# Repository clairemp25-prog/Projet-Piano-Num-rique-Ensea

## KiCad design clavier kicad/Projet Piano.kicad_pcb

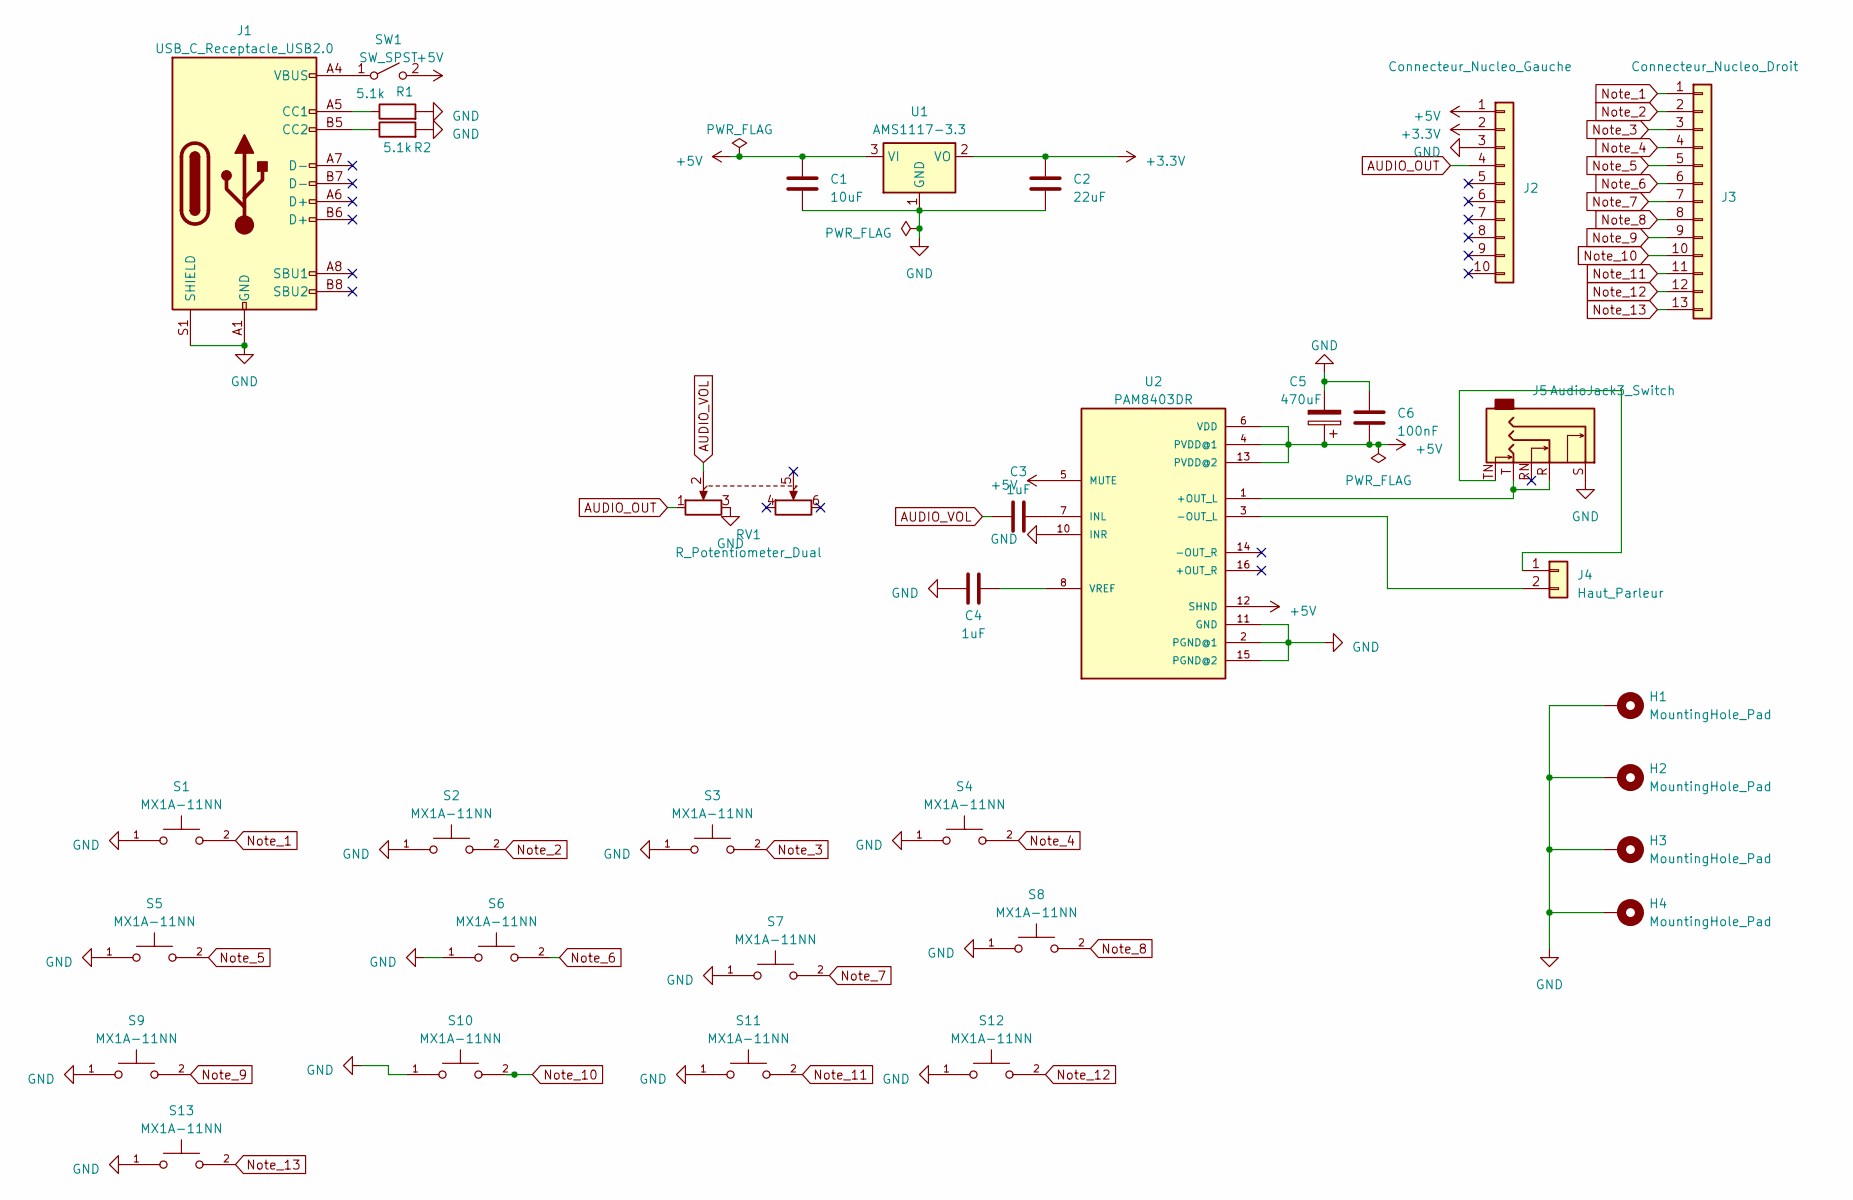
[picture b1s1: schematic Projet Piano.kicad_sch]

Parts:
C1: 10uF; CP_Radial_D5.0mm_P2.00mm
C2: 22uF; CP_Radial_D5.0mm_P2.00mm
C3, C4: 1uF; C_Disc_D5.0mm_W2.5mm_P5.00mm
C5: 470uF; CP_Radial_D8.0mm_P3.50mm
C6: 100nF; C_Disc_D3.0mm_W1.6mm_P2.50mm
H1, H2, H3, H4: MountingHole_Pad; MountingHole_3.2mm_M3_Pad
J1: USB_C_Receptacle_USB2.0; USB_C_Receptacle_GCT_USB4105-xx-A_16P_TopMnt_Horizontal
J2: Connecteur_Nucleo_Gauche; PinHeader_1x10_P2.54mm_Vertical
J3: Connecteur_Nucleo_Droit; PinHeader_1x13_P2.54mm_Vertical
J4: Haut_Parleur; PinHeader_1x02_P2.54mm_Vertical
J5: AudioJack3_Switch; Jack_3.5mm_CUI_SJ1-3525N_Horizontal
R1, R2: 5.1k; R_Axial_DIN0207_L6.3mm_D2.5mm_P7.62mm_Horizontal
RV1: R_Potentiometer_Dual; Potentiometer_Alps_RK163_Dual_Horizontal
S1, S2, S3, S4, S5, S6, S7, S8, S9, S10, S11, S12, S13: MX1A-11NN; SW_Cherry_MX_1.00u_PCB
SW1: SW_SPST; PinHeader_1x02_P2.54mm_Vertical
U1: AMS1117-3.3; SOT-223-3_TabPin2
U2: PAM8403DR; SO-16_3.9x9.9mm_P1.27mm

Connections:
+3.3V: C2.2, J2.2, U1.2 (VO)
+5V: C1.2, C5.1, C6.2, J2.1, SW1.2 (B), U1.3 (VI), U2.4 (PVDD@1), U2.5 (MUTE), U2.6 (VDD), U2.12 (SHND), U2.13 (PVDD@2)
AUDIO_OUT: J2.4, RV1.1
AUDIO_VOL: C3.1, RV1.2
GND: C1.1, C2.1, C4.1, C5.2, C6.1, H1.1, H2.1, H3.1, H4.1, J1.A1 (GND), J1.A12 (GND), J1.B1 (GND), J1.B12 (GND), J1.S1 (SHIELD), J2.3, J5.S, R1.2, R2.2, RV1.3, S1.1, S2.1, S3.1, S4.1, S5.1, S6.1, S7.1, S8.1, S9.1, S10.1, S11.1, S12.1, S13.1, U1.1 (GND), U2.2 (PGND@1), U2.10 (INR), U2.11 (GND), U2.15 (PGND@2)
unnamed: J1.A5 (CC1), R1.1
unnamed: J1.B5 (CC2), R2.1
unnamed: J4.1, J5.TN
unnamed: J4.2, U2.3 (-OUT_L)
unnamed: J1.A4 (VBUS), J1.A9 (VBUS), J1.B4 (VBUS), J1.B9 (VBUS), SW1.1 (A)
unnamed: J5.R, J5.T, U2.1 (+OUT_L)
unnamed: C3.2, U2.7 (INL)
unnamed: C4.2, U2.8 (VREF)
Note_1: J3.1, S1.2
Note_2: J3.2, S2.2
Note_3: J3.3, S3.2
Note_4: J3.4, S4.2
Note_5: J3.5, S5.2
Note_6: J3.6, S6.2
Note_7: J3.7, S7.2
Note_8: J3.8, S8.2
Note_9: J3.9, S9.2
Note_10: J3.10, S10.2
Note_11: J3.11, S11.2
Note_12: J3.12, S12.2
Note_13: J3.13, S13.2

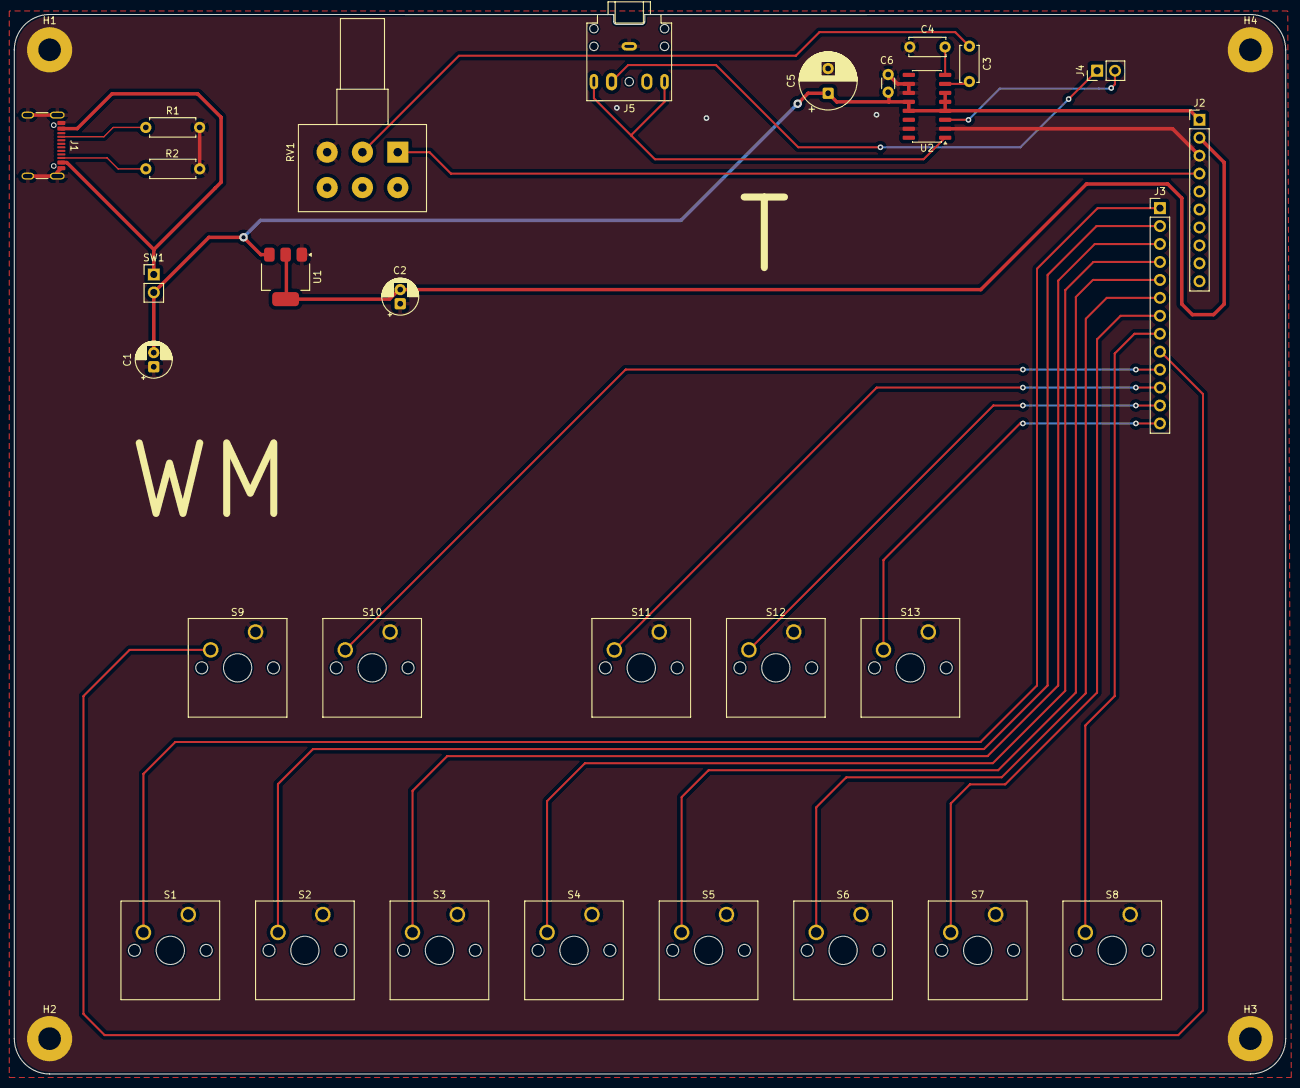
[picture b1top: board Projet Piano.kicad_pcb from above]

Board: 2 copper layers, 180.0 x 150.0 mm, 34 parts (0 on the bottom side), 26 nets.

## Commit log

2026-05-28 Create Rapport
